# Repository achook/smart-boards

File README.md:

# smart-boards

Eagle files for my IoT projects

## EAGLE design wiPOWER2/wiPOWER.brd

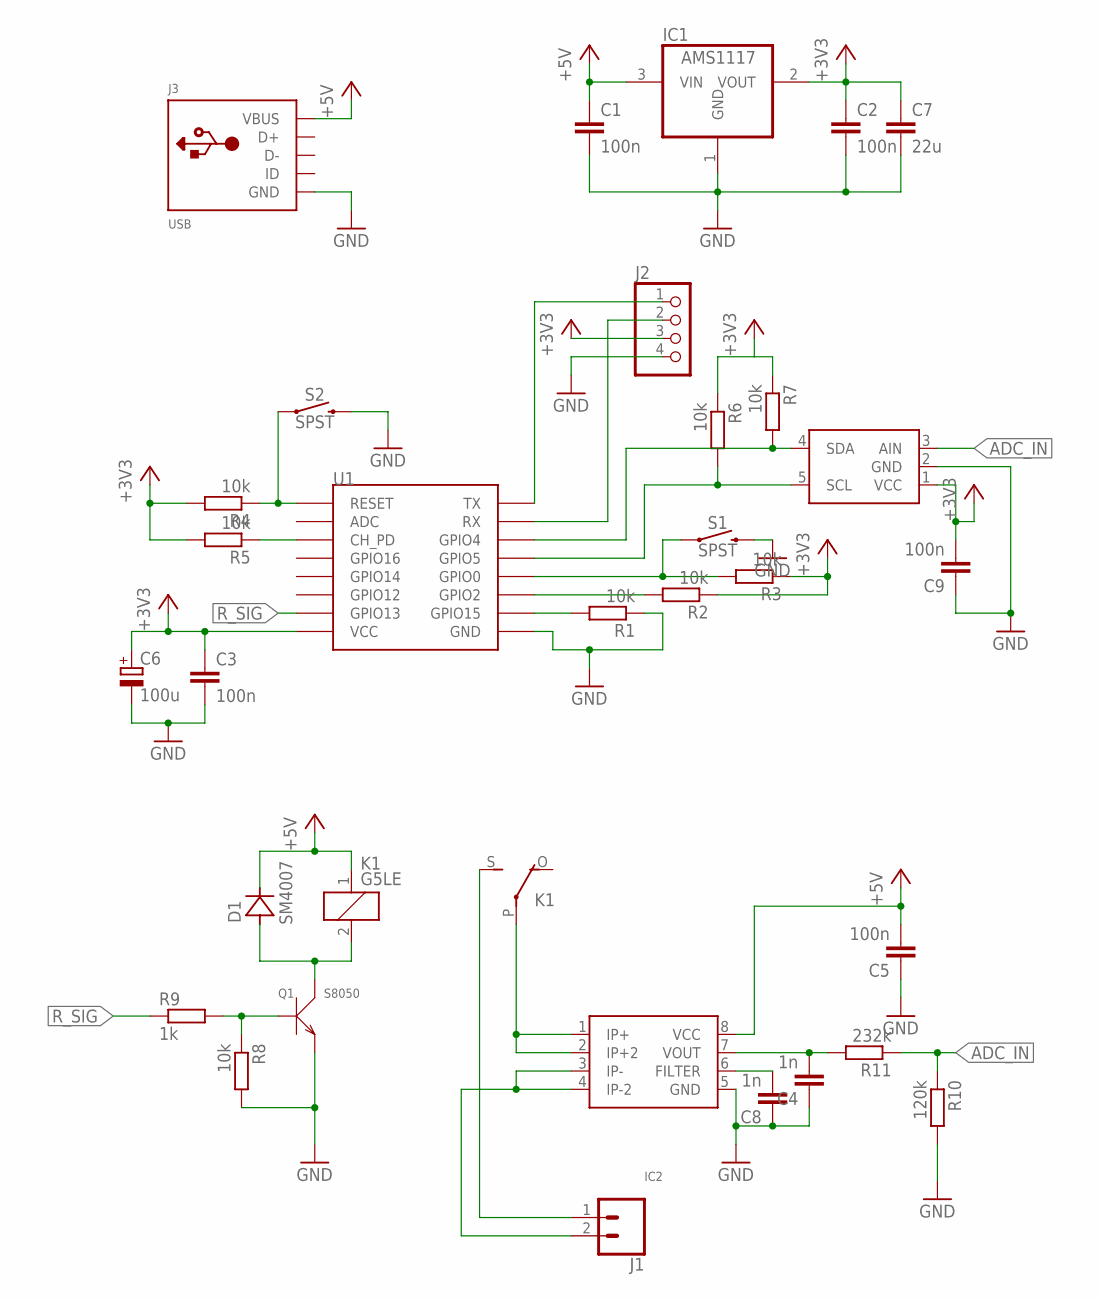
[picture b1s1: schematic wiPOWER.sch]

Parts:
C1, C2, C3, C5, C9: 100n; C0603
C4, C8: 1n; C0603
C6: 100u; B/3528-21R
C7: 22u; C0603
D1: SM4007; DIODE_SOD123
IC1: AMS1117; SOT223
IC2: ACS724; SOIC8
J1: CONN_025MM; SCREWTERMINAL-5MM-2
J2: PINHD-1X4; 1X04
J3: USB; MIC-USB
K1: G5LE
Q1: S8050; SOT-23
R1, R2, R3, R4, R5, R6, R7, R8: 10k; R0603
R9: 1k; R0603
R10: 120k; R0603
R11: 232k; R0603
S1, S2: SPST; TACTILE_SWITCH_SMD_6.0X3.5MM
U1: ESP12SMD; ESP12-SMD
U$1: MCP3221SOT23-5; GHI-IC_SOT23-5(MICROCHIP)

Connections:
+3V3: C2.1, C3.1, C6.+, C7.1, C9.2, IC1.2 (VOUT), J2.3, R2.1, R3.1, R4.2, R5.2, R6.1, R7.1, U1.VCC, U$1.1 (VCC)
+5V: C1.1, C5.2, D1.C, IC1.3 (VIN), IC2.8 (VCC), J3.P$5 (VBUS), K1.1
ADC_IN: R10.1, R11.1, U$1.3 (AIN)
GND: C1.2, C2.2, C3.2, C4.1, C5.1, C6.-, C7.2, C8.1, C9.1, IC1.1 (GND), IC2.5 (GND), J2.4, J3.P$2 (GND), Q1.2 (E), R1.1, R8.2, R10.2, S1.2, S2.2, U1.GND, U$1.2 (GND)
IP+: IC2.1 (IP+), IC2.2 (IP+2), K1.P
IP-: IC2.3 (IP-), IC2.4 (IP-2), J1.2
unnamed: J2.1, U1.TXD0 (TX)
unnamed: J2.2, U1.RXD0 (RX)
unnamed: C8.2, IC2.6 (FILTER)
unnamed: R4.1, S2.1, U1.RESET
unnamed: C4.2, IC2.7 (VOUT), R11.2
unnamed: R6.2, U1.GPIO5, U$1.5 (SCL)
unnamed: R5.1, U1.CH_PD
unnamed: R7.2, U1.GPIO4, U$1.4 (SDA)
unnamed: R1.2, U1.GPIO15
unnamed: R2.2, U1.GPIO2
unnamed: R3.2, S1.1, U1.GPIO0
unnamed: D1.A, K1.2, Q1.3 (C)
unnamed: Q1.1 (B), R8.1, R9.2
PRE_IP+: J1.1, K1.S
R_SIG: R9.1, U1.GPIO13

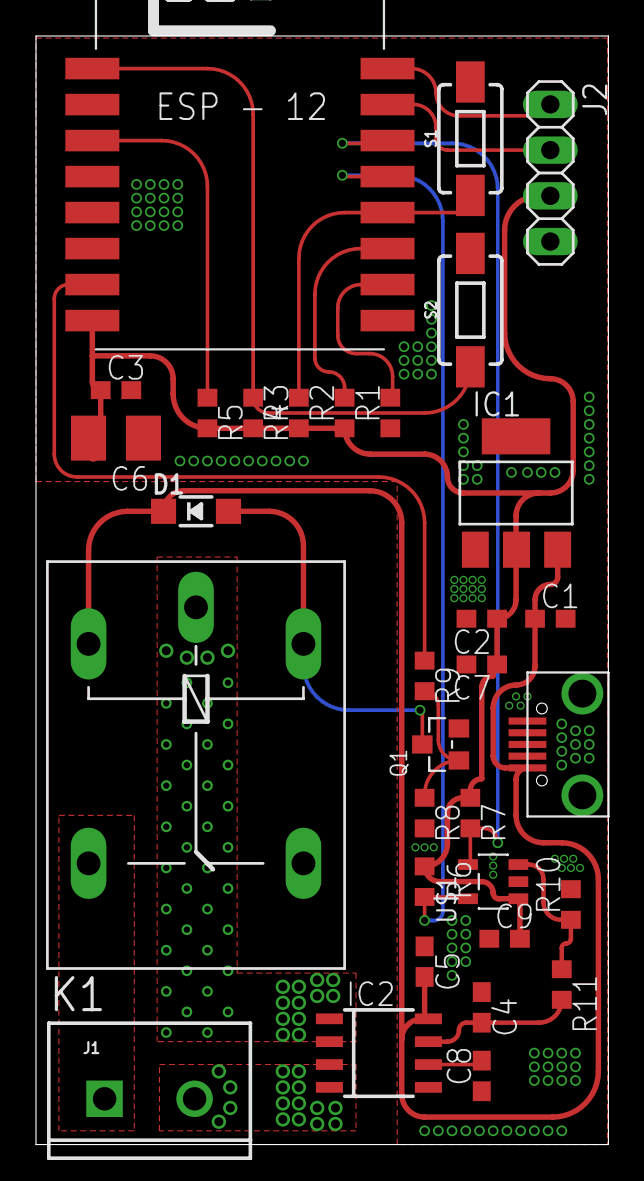
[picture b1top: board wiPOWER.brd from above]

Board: 2 copper layers, 31.8 x 61.6 mm, 32 parts (0 on the bottom side), 21 nets.

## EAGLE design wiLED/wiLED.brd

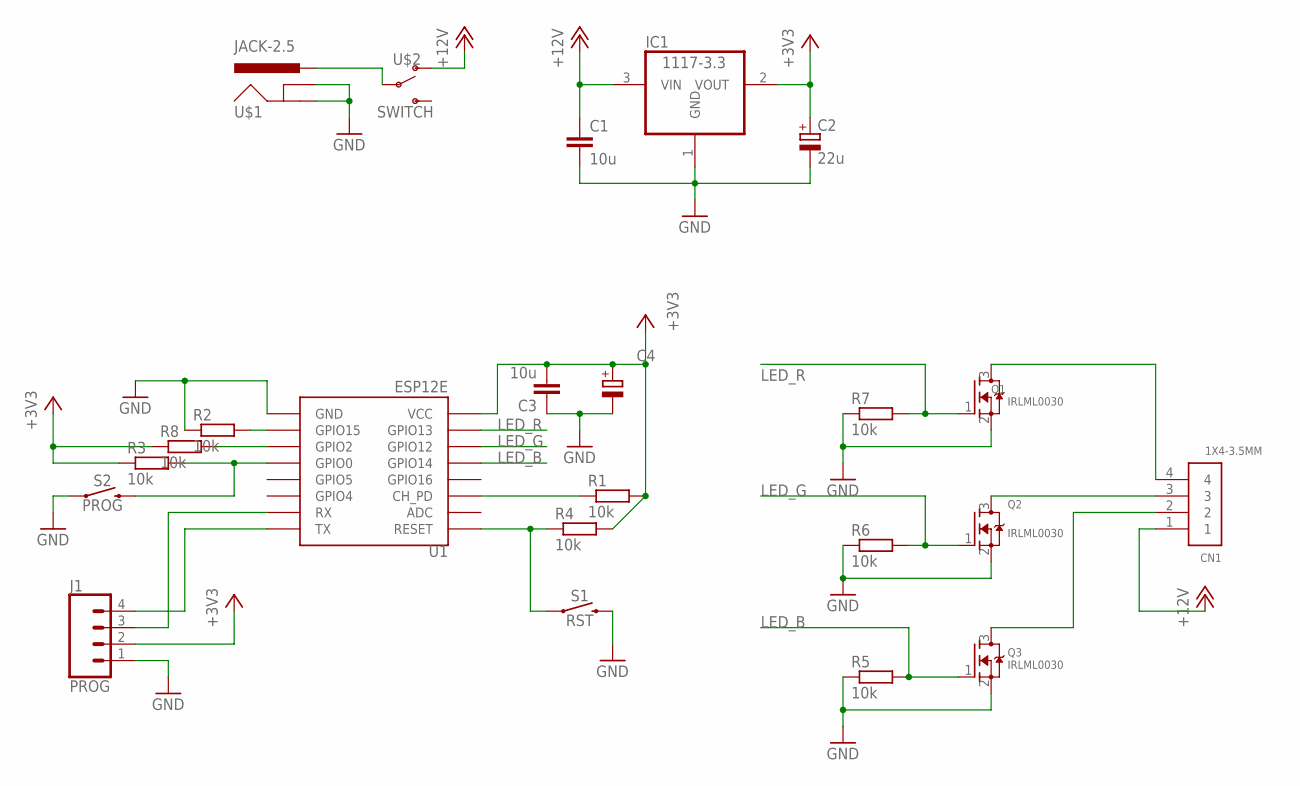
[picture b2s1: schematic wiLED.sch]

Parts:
C1, C3: 10u; C0805
C2: 22u; SMC_A
C4: CPOL-EUSMCC; SMC_C
CN1: 1X4-3.5MM; 1X04-3.5MM
IC1: 1117-3.3; SOT223
J1: PROG; 1X04
Q1, Q2, Q3: IRLML0030; SOT23
R1, R2, R3, R4, R5, R6, R7, R8: 10k; M0805
S1: RST; TACTILE_SWITCH_SMD_6.0X3.5MM
S2: PROG; TACTILE_SWITCH_SMD_6.0X3.5MM
U1: ESP12E; ESP12-SMD
U$1: JACK-2.5; DC-2.5
U$2: SWITCH

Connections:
+3V3: C2.+, C3.2, C4.+, IC1.2 (VOUT), J1.2, R1.2, R3.1, R4.2, R8.1, U1.VCC
+12V: C1.1, CN1.1, IC1.3 (VIN), U$2.P$1 (O)
GND: C1.2, C2.-, C3.1, C4.-, IC1.1 (GND), J1.1, Q1.2 (S), Q2.2 (S), Q3.2 (S), R2.1, R5.1, R6.1, R7.1, S1.2, S2.1, U1.GND, U$1.P$1 (GND), U$1.P$3 (GNDBREAK)
LED_B: Q3.1 (G), R5.2, U1.GPIO14
LED_G: Q2.1 (G), R6.2, U1.GPIO12
LED_R: Q1.1 (G), R7.2, U1.GPIO13
unnamed: U$1.P$2 (PWR), U$2.P$2
unnamed: R2.2, U1.GPIO15
unnamed: R3.2, S2.2, U1.GPIO0
unnamed: CN1.4, Q1.3 (D)
unnamed: R1.1, U1.CH_PD
unnamed: CN1.3, Q2.3 (D)
unnamed: J1.3, U1.RXD0 (RX)
unnamed: J1.4, U1.TXD0 (TX)
unnamed: CN1.2, Q3.3 (D)
unnamed: R8.2, U1.GPIO2
unnamed: R4.1, S1.1, U1.RESET

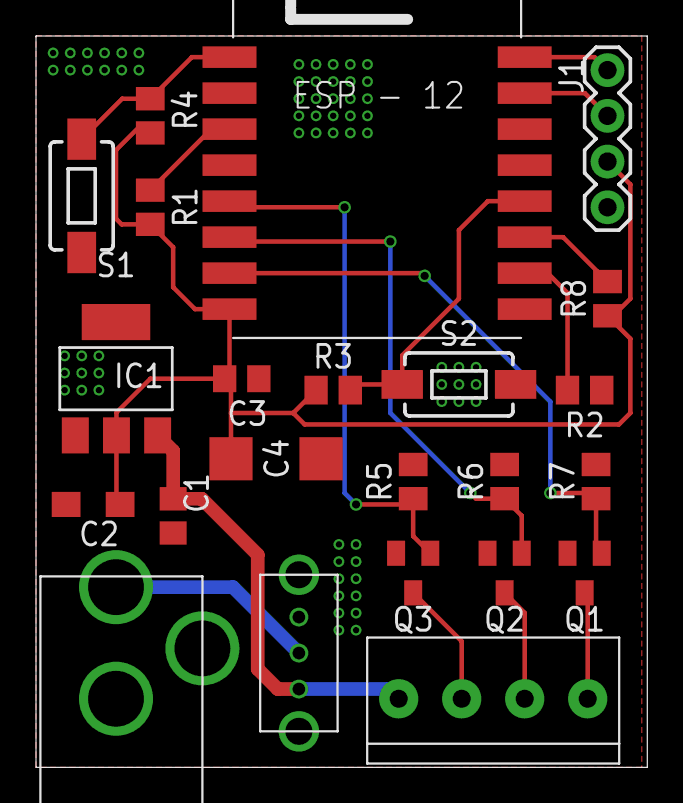
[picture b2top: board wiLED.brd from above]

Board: 2 copper layers, 34.0 x 40.6 mm, 23 parts (0 on the bottom side), 17 nets.

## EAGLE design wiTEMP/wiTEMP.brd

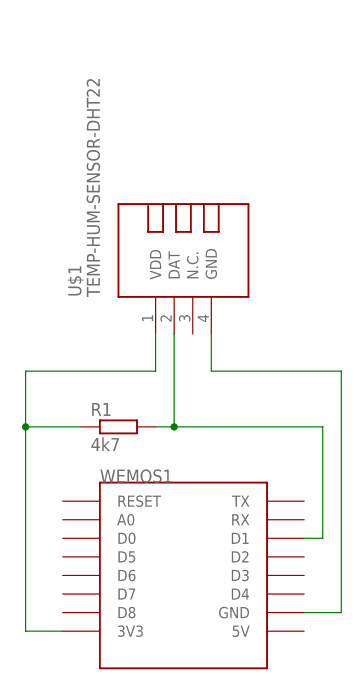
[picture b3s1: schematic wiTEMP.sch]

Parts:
R1: 4k7; 0207/10
U$1: TEMP-HUM-SENSOR-DHT22
WEMOS1: WEMOS-D1-MINI

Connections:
unnamed: R1.1, U$1.1 (VDD), WEMOS1.3V3
unnamed: U$1.4 (GND), WEMOS1.GND
unnamed: R1.2, U$1.2 (DAT), WEMOS1.D1

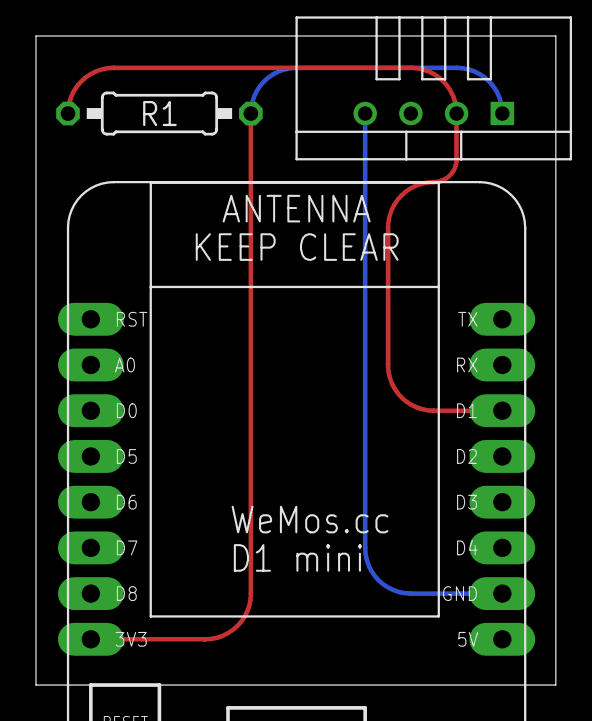
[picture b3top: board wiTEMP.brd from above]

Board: 2 copper layers, 28.9 x 36.1 mm, 3 parts (0 on the bottom side), 3 nets.

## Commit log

2020-07-27 Remove zip files
2020-07-27 Add license and readme
2020-07-28 wiPOWER2: Add power traces

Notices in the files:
wiLED/wiLED.brd:
©Karol Kucza
parts and their libraries:
SparkFun-Connectors: Licensing: Creative Commons ShareAlike 4.0 International - https://creativecommons.org/licenses/by-sa/4.0
diy-modules: Released under the Creative Commons Attribution 4.0 International License: http://creativecommons.org/licenses/by/4.0
